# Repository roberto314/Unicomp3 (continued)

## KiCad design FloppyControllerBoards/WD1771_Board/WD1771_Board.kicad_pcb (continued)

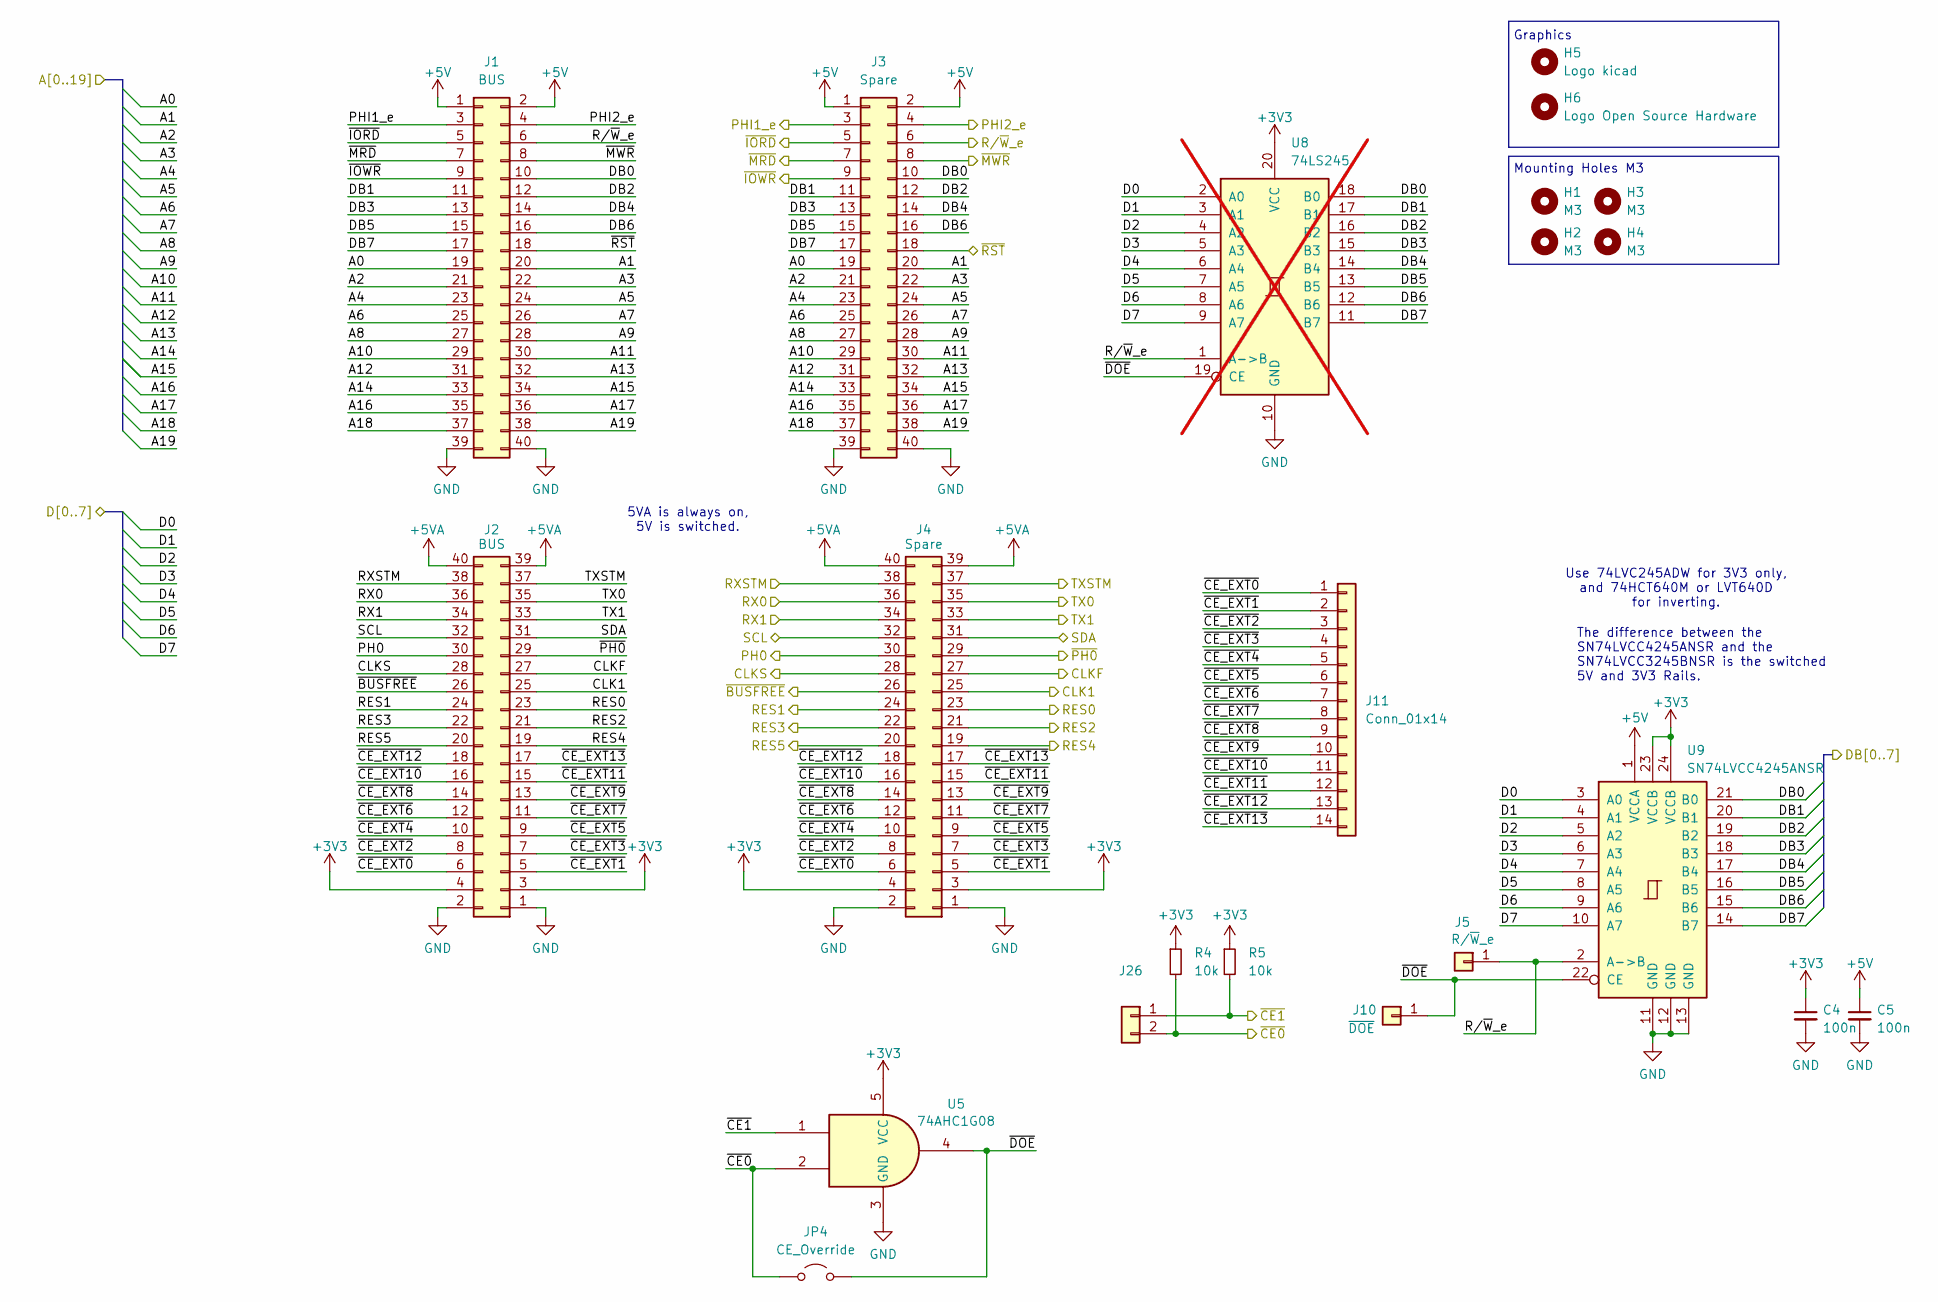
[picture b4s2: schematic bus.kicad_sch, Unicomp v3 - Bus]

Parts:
C4, C5: 100n; C_1206_3216Metric
H1, H2, H3, H4: M3; MountingHole_3.2mm_M3
H5: Logo kicad; KiCad-Logo2_6mm_SilkScreen
H6: Logo Open Source Hardware; OSHW-Logo2_7.3x6mm_SilkScreen
J1, J2: BUS; PinSocket_2x20_P2.54mm_Vertical
J3, J4: Spare; PinSocket_2x20_P2.54mm_Vertical
J5: R/~{W}_e; PinHeader_1x01_P2.00mm_Vertical
J10: ~{DOE}; PinHeader_1x01_P2.00mm_Vertical
J11: Conn_01x14; PinSocket_1x14_P2.54mm_Vertical
J26: Conn_01x02; PinSocket_1x02_P2.54mm_Vertical
JP4: CE_Override; SolderJumper-2_P1.3mm_Open_RoundedPad1.0x1.5mm
R4, R5: 10k; R_1206_3216Metric_Pad1.30x1.75mm_HandSolder
U5: 74AHC1G08; SOT-23-5_HandSoldering
U8: 74LS245; SOIC-20W_7.5x12.8mm_P1.27mm; not fitted
U9: SN74LVCC4245ANSR; SO-24_5.3x15mm_P1.27mm

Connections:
+3V3: C4.1, J2.3, J2.4, J4.3, J4.4, R4.1, R5.1, U5.5 (VCC), U8.20 (VCC), U9.23 (VCCB), U9.24 (VCCB); also elsewhere on the board
+5V: C5.1, J1.1, J1.2, J3.1, J3.2, U9.1 (VCCA); also elsewhere on the board
+5VA: J2.39, J2.40, J4.39, J4.40; also elsewhere on the board
/A0: J1.19, J3.19; also elsewhere on the board
/A1: J1.20, J3.20; also elsewhere on the board
/A2: J1.21, J3.21
/A3: J1.22, J3.22; also elsewhere on the board
/A4: J1.23, J3.23
/A5: J1.24, J3.24
/A6: J1.25, J3.25
/A7: J1.26, J3.26
/A8: J1.27, J3.27
/A9: J1.28, J3.28
/A10: J1.29, J3.29
/A11: J1.30, J3.30
/A12: J1.31, J3.31
/A13: J1.32, J3.32
/A14: J1.33, J3.33
/A15: J1.34, J3.34
/A16: J1.35, J3.35
/A17: J1.36, J3.36
/A18: J1.37, J3.37
/A19: J1.38, J3.38
/Bus/~CE_EXT0: J2.6, J4.6, J11.1
/Bus/~CE_EXT1: J2.5, J4.5, J11.2
/Bus/~CE_EXT2: J2.8, J4.8, J11.3
/Bus/~CE_EXT3: J2.7, J4.7, J11.4
/Bus/~CE_EXT4: J2.10, J4.10, J11.5
/Bus/~CE_EXT5: J2.9, J4.9, J11.6
/Bus/~CE_EXT6: J2.12, J4.12, J11.7
/Bus/~CE_EXT7: J2.11, J4.11, J11.8
/Bus/~CE_EXT8: J2.14, J4.14, J11.9
/Bus/~CE_EXT9: J2.13, J4.13, J11.10
/Bus/~CE_EXT10: J2.16, J4.16, J11.11
/Bus/~CE_EXT11: J2.15, J4.15, J11.12
/Bus/~CE_EXT12: J2.18, J4.18, J11.13
/Bus/~CE_EXT13: J2.17, J4.17, J11.14
/Bus/~DOE: J10.1, JP4.2 (B), U5.4, U8.19 (CE), U9.22 (CE)
/CLK1: J2.25, J4.25; also elsewhere on the board
/CLKF: J2.27, J4.27
/CLKS: J2.28, J4.28
/D0: U8.2 (A0), U9.3 (A0); also elsewhere on the board
/D1: U8.3 (A1), U9.4 (A1); also elsewhere on the board
/D2: U8.4 (A2), U9.5 (A2); also elsewhere on the board
/D3: U8.5 (A3), U9.6 (A3); also elsewhere on the board
/D4: U8.6 (A4), U9.7 (A4); also elsewhere on the board
/D5: U8.7 (A5), U9.8 (A5); also elsewhere on the board
/D6: U8.8 (A6), U9.9 (A6); also elsewhere on the board
/D7: U8.9 (A7), U9.10 (A7); also elsewhere on the board
/DB0: J1.10, J3.10, U8.18 (B0), U9.21 (B0); also elsewhere on the board
/DB1: J1.11, J3.11, U8.17 (B1), U9.20 (B1); also elsewhere on the board
/DB2: J1.12, J3.12, U8.16 (B2), U9.19 (B2); also elsewhere on the board
/DB3: J1.13, J3.13, U8.15 (B3), U9.18 (B3); also elsewhere on the board
/DB4: J1.14, J3.14, U8.14 (B4), U9.17 (B4); also elsewhere on the board
/DB5: J1.15, J3.15, U8.13 (B5), U9.16 (B5); also elsewhere on the board
/DB6: J1.16, J3.16, U8.12 (B6), U9.15 (B6); also elsewhere on the board
/DB7: J1.17, J3.17, U8.11 (B7), U9.14 (B7); also elsewhere on the board
/PH0: J2.30, J4.30
/PHI1_e: J1.3, J3.3
/PHI2_e: J1.4, J3.4; also elsewhere on the board
/RES0: J2.23, J4.23
/RES1: J2.24, J4.24
/RES2: J2.21, J4.21
/RES3: J2.22, J4.22
/RES4: J2.19, J4.19
/RES5: J2.20, J4.20
/RX0: J2.36, J4.36
/RX1: J2.34, J4.34
/RXSTM: J2.38, J4.38
/R/~W_e: J1.6, J3.6, J5.1, U8.1 (A->B), U9.2 (A->B); also elsewhere on the board
/SCL: J2.32, J4.32
/SDA: J2.31, J4.31
/TX0: J2.35, J4.35
/TX1: J2.33, J4.33
/TXSTM: J2.37, J4.37
/ZZ27: J26.2, JP4.1 (A), R4.2, U5.2; also elsewhere on the board
/ZZ40: J1.18, J3.18; also elsewhere on the board
/~BUSFREE: J2.26, J4.26
/~CE1: J26.1, R5.2, U5.1
/~IORD: J1.5, J3.5; also elsewhere on the board
/~IOWR: J1.9, J3.9; also elsewhere on the board
/~MRD: J1.7, J3.7
/~MWR: J1.8, J3.8
/~PH0: J2.29, J4.29
GND: C4.2, C5.2, J1.39, J1.40, J2.1, J2.2, J3.39, J3.40, J4.1, J4.2, U5.3 (GND), U8.10 (GND), U9.11 (GND), U9.12 (GND), U9.13 (GND); also elsewhere on the board

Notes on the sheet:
Graphics
5VA is always on, 5V is switched.
Use 74LVC245ADW for 3V3 only, and 74HCT640M or LVT640D for inverting.
Mounting Holes M3
The difference between the SN74LVCC4245ANSR and the SN74LVCC3245BNSR is the switched 5V and 3V3 Rails.

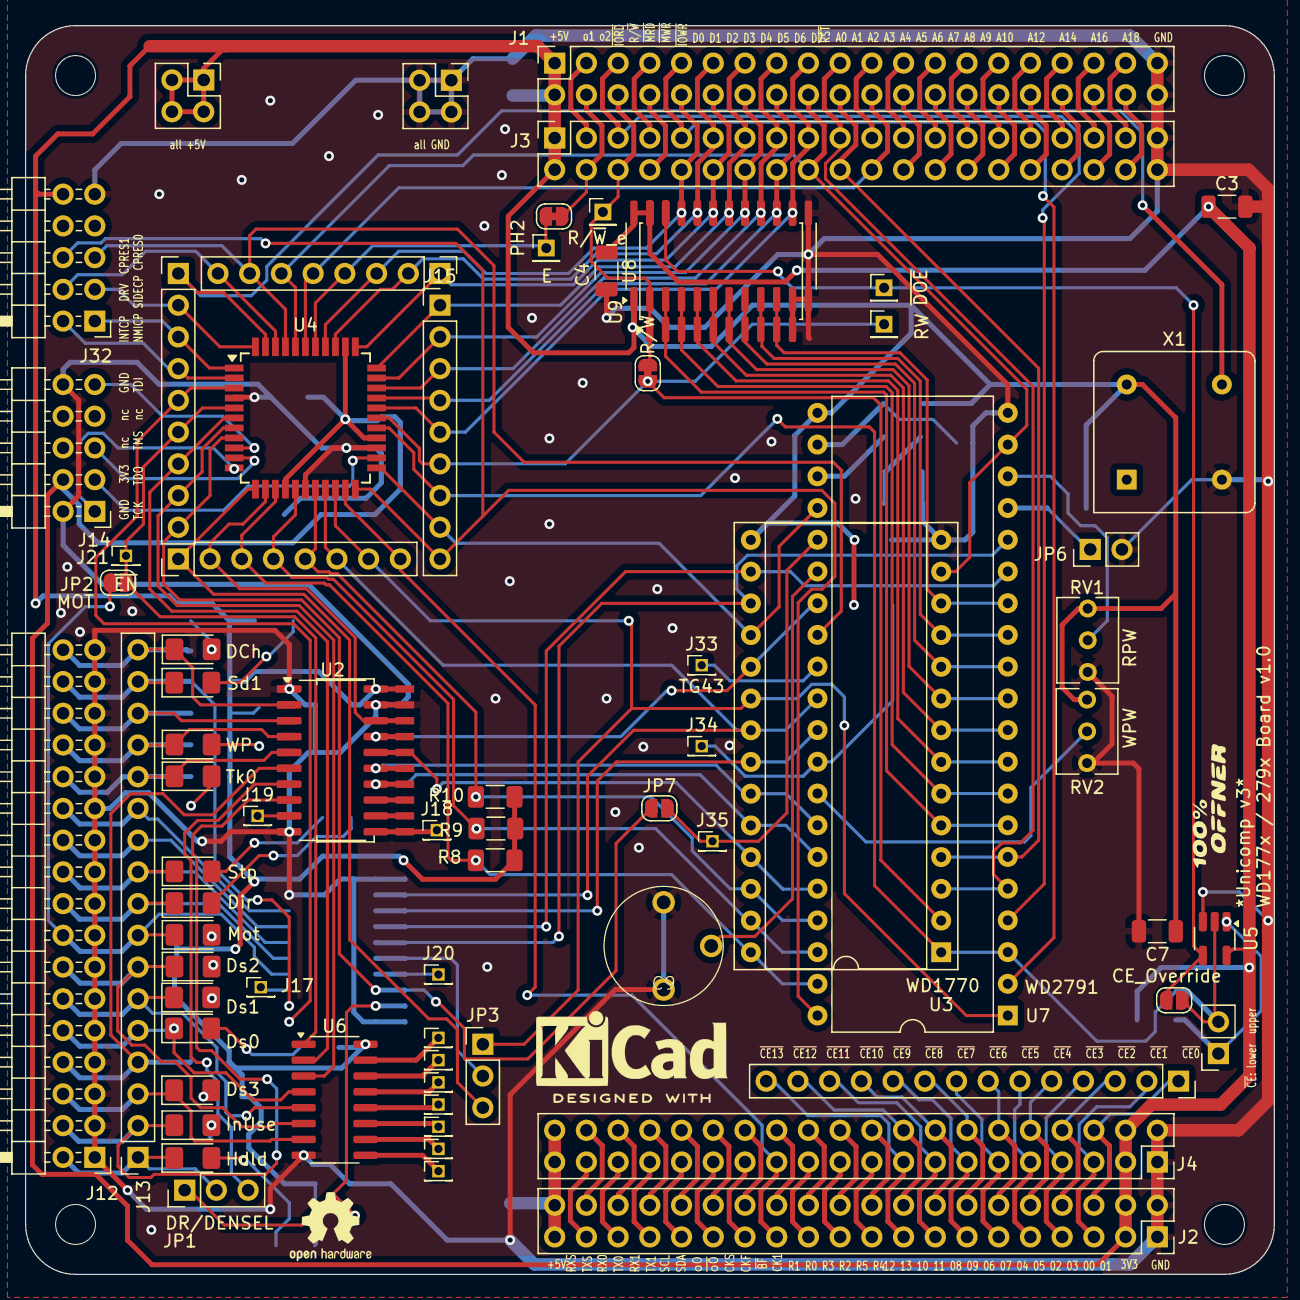
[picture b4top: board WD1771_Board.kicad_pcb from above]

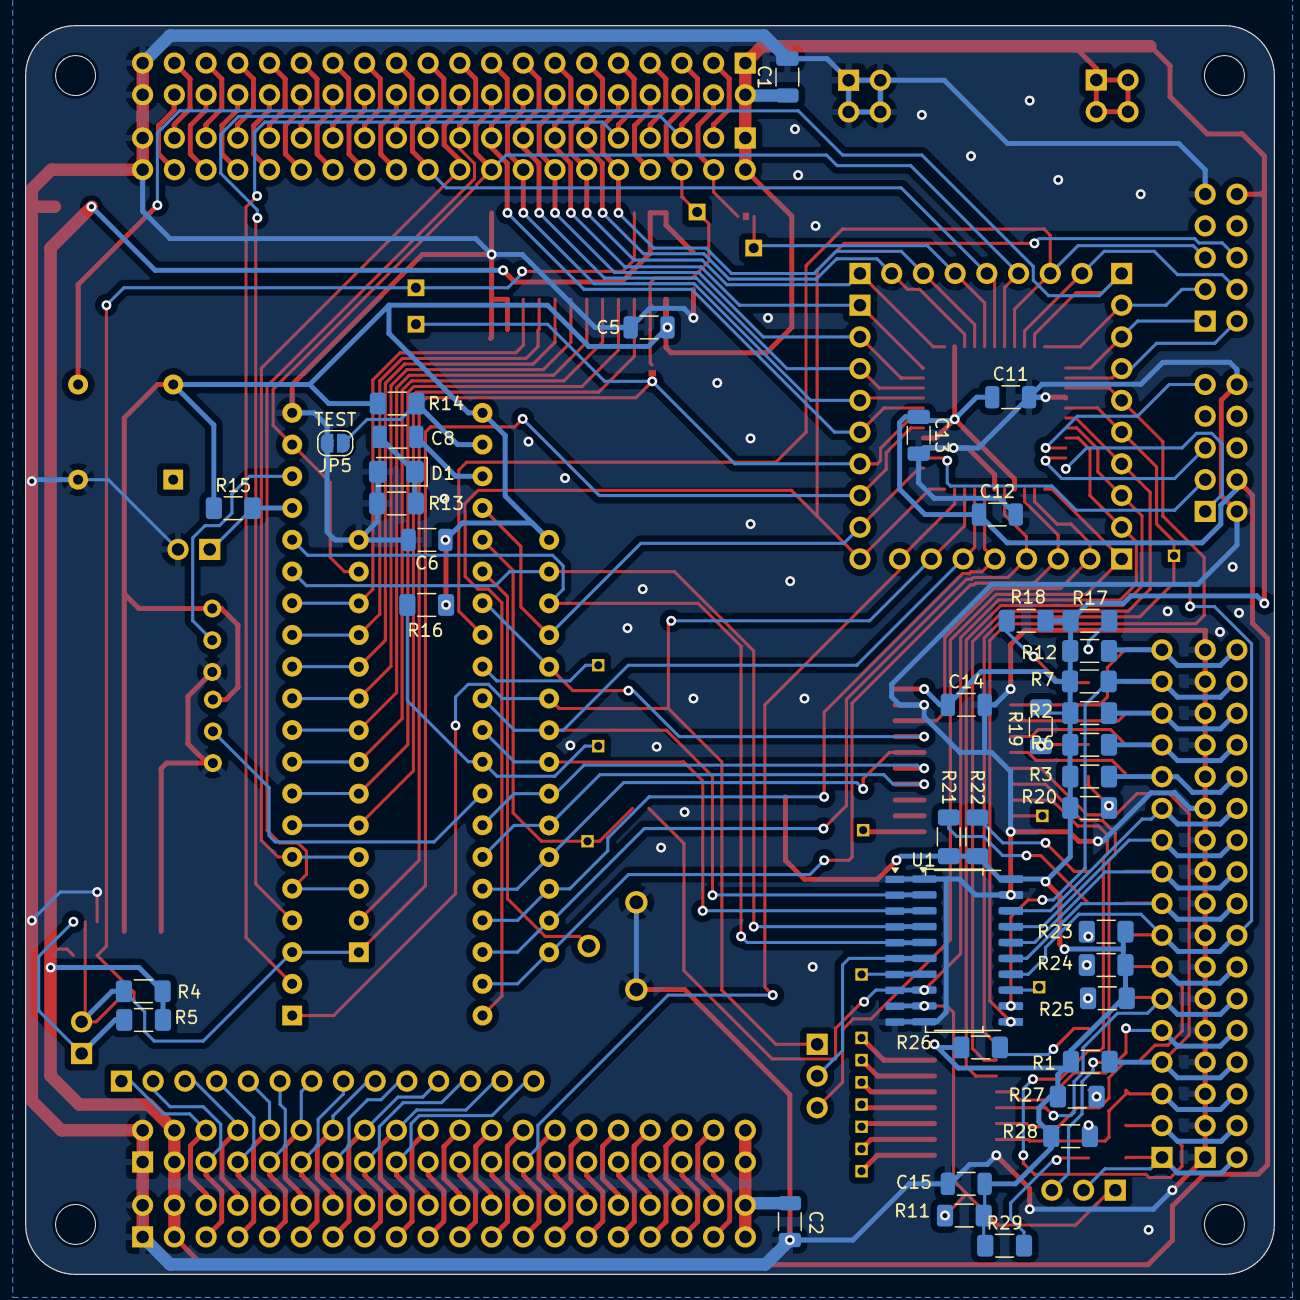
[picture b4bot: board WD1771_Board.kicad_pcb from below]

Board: 2 copper layers, 100.0 x 100.0 mm, 121 parts (40 on the bottom side), 174 nets.

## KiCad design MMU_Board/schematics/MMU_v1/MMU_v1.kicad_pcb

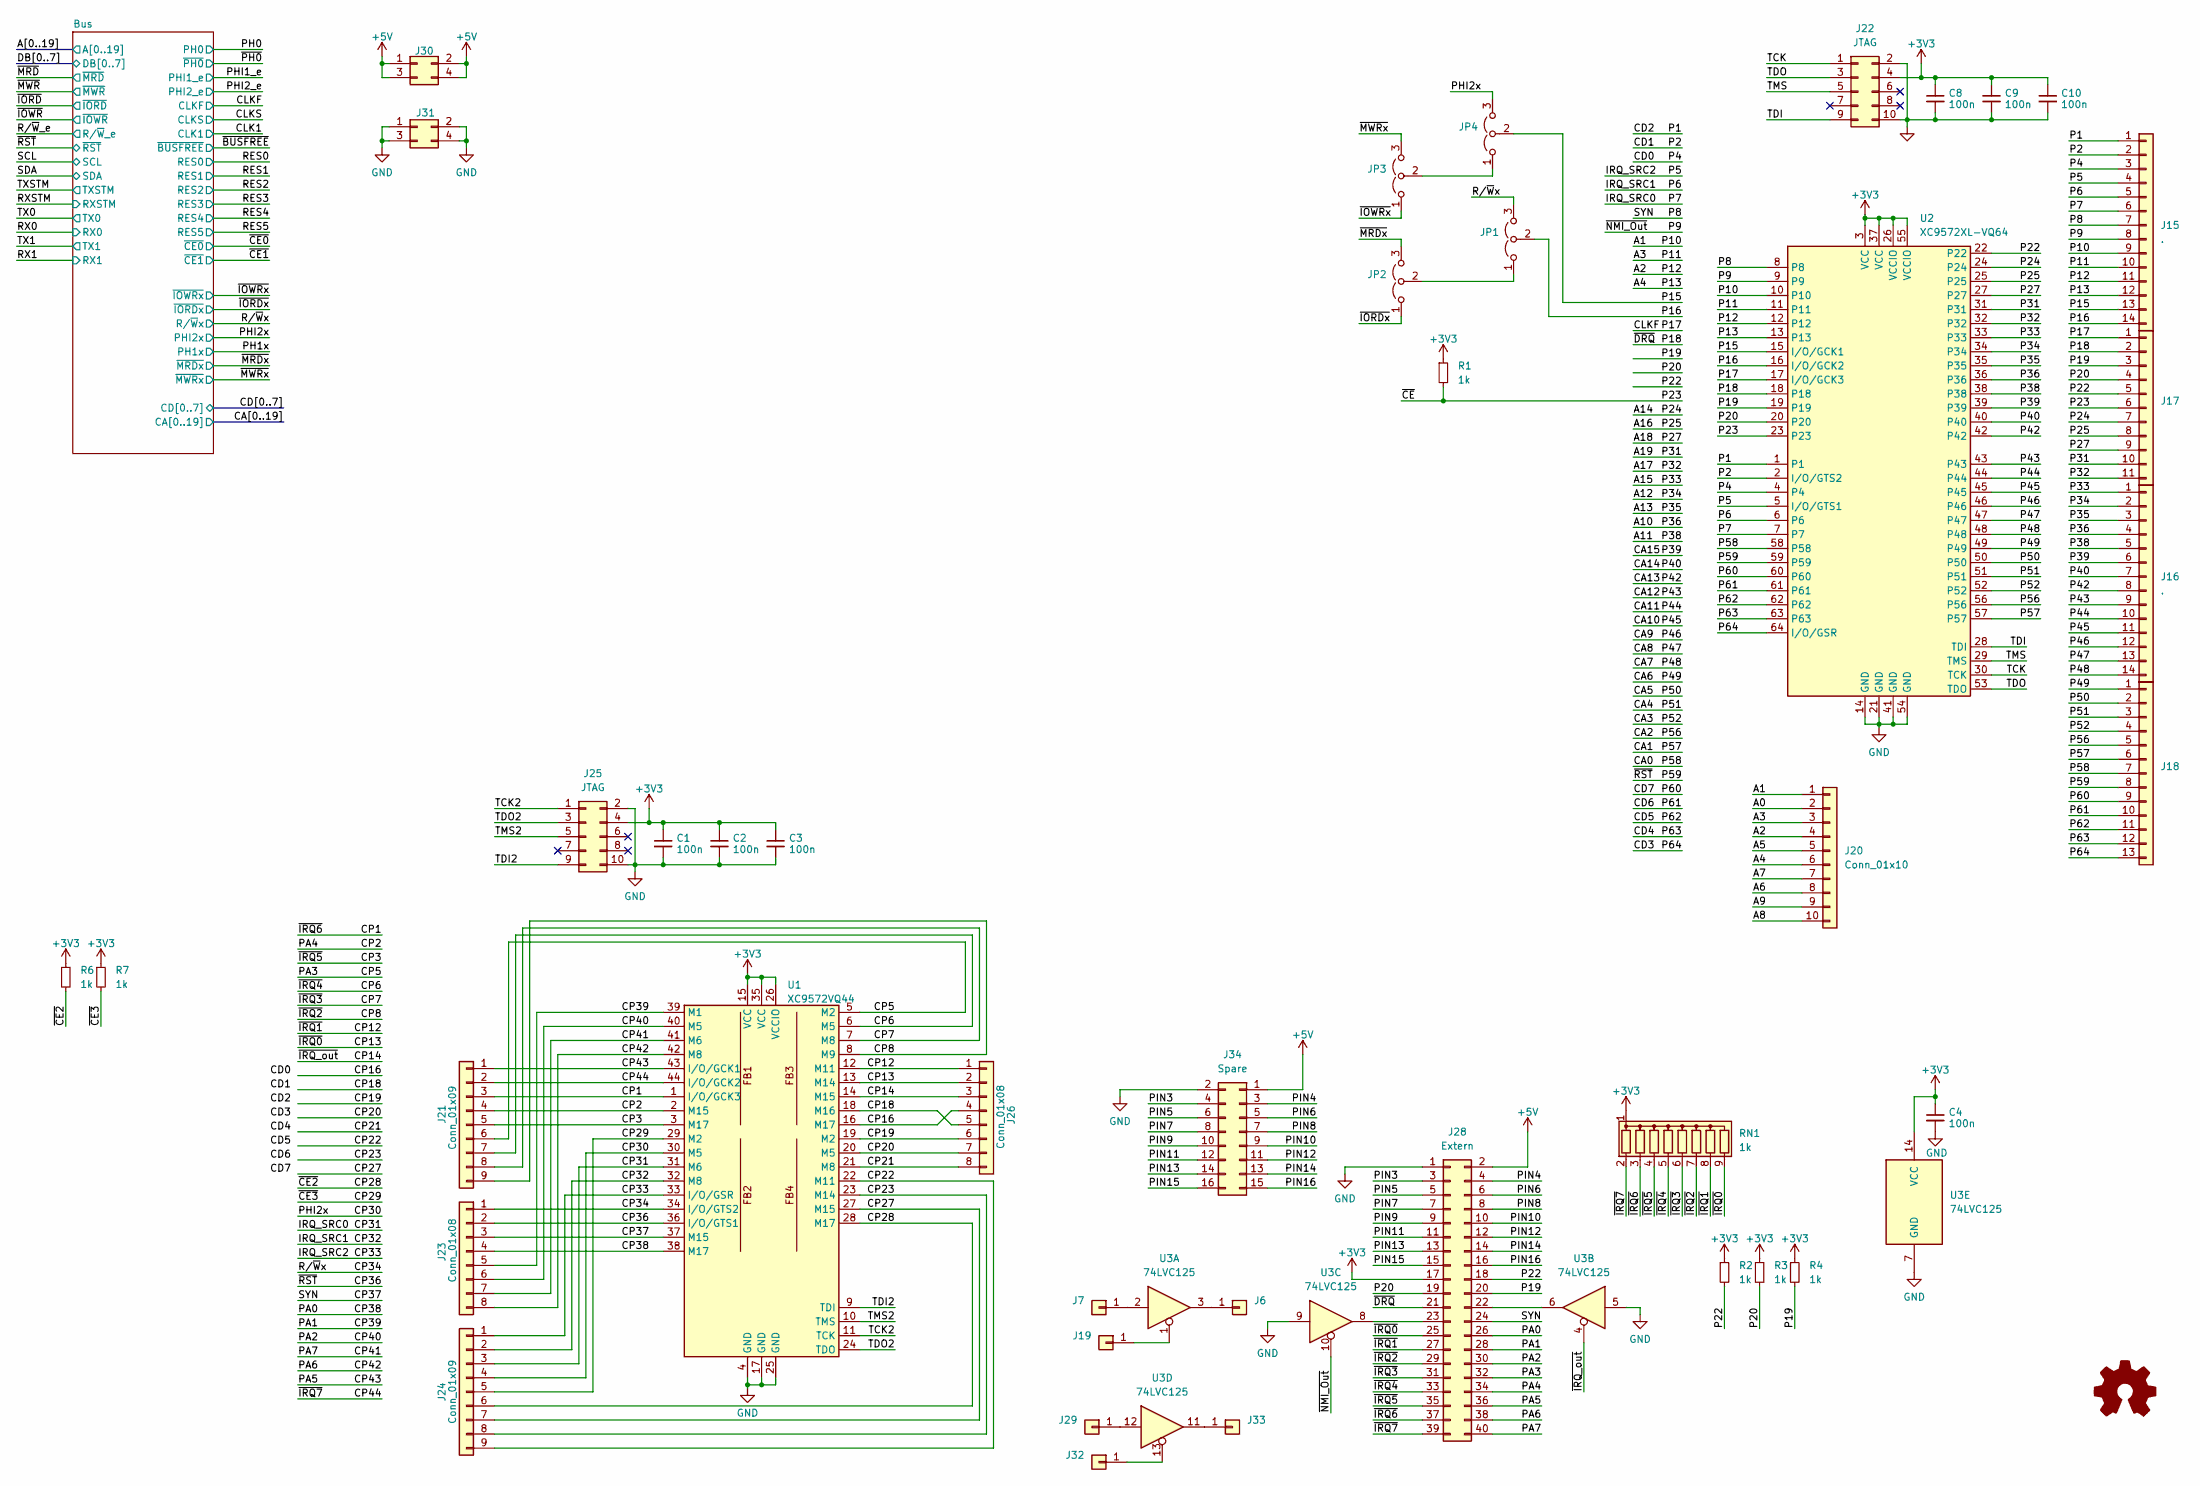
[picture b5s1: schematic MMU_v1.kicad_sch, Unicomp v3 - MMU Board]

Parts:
C1, C2, C3, C4, C8, C9, C10: 100n; C_1206_3216Metric
J6, J7, J19, J29, J32, J33: Conn_01x01; PinSocket_1x01_P1.27mm_Vertical
J15, J16: .; PinSocket_1x14_P2.00mm_Vertical
J17: Conn_01x11; PinSocket_1x11_P2.00mm_Vertical
J18: Conn_01x13; PinSocket_1x13_P2.00mm_Vertical
J20: Conn_01x10; PinSocket_1x10_P2.00mm_Vertical
J21, J24: Conn_01x09; PinHeader_1x09_P2.54mm_Vertical
J22, J25: JTAG; PinHeader_2x05_P2.54mm_Horizontal
J23, J26: Conn_01x08; PinHeader_1x08_P2.54mm_Vertical
J28: Extern; PinHeader_2x20_P2.54mm_Horizontal
J30, J31: Conn_02x02_Odd_Even; PinSocket_2x02_P2.54mm_Vertical
J34: Spare; PinSocket_2x08_P2.54mm_Vertical
JP1, JP2, JP3, JP4: Jumper_3_Open; SolderJumper-3_P1.3mm_Open_RoundedPad1.0x1.5mm
R1, R2, R3, R4, R6, R7: 1k; R_1206_3216Metric_Pad1.30x1.75mm_HandSolder
RN1: 1k; R_Array_SIP9
U1: XC9572VQ44; TQFP-44_10x10mm_P0.8mm
U2: XC9572XL-VQ64; TQFP-64_10x10mm_P0.5mm
U3: 74LVC125; SOIC-14_3.9x8.7mm_P1.27mm

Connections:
+3V3: C1.1, C2.1, C3.1, C4.1, C8.1, C9.1, C10.1, J22.4, J25.4, J28.17, R1.1, R2.1, R3.1, R4.1, R6.1, R7.1, RN1.1 (common), U1.15 (VCC), U1.26 (VCCIO), U1.35 (VCC), U2.3 (VCC), U2.26 (VCCIO), U2.37 (VCC), U2.55 (VCCIO), U3.14 (VCC); also elsewhere on the board
+5V: J28.2, J30.1, J30.2, J30.3, J30.4, J34.1; also elsewhere on the board
/A0: J20.2; also elsewhere on the board
/A1: J15.9, J20.1, U2.10; also elsewhere on the board
/A2: J15.11, J20.4, U2.12; also elsewhere on the board
/A3: J15.10, J20.3, U2.11; also elsewhere on the board
/A4: J15.12, J20.6, U2.13; also elsewhere on the board
/A5: J20.5; also elsewhere on the board
/A6: J20.8; also elsewhere on the board
/A7: J20.7; also elsewhere on the board
/A8: J20.10; also elsewhere on the board
/A9: J20.9; also elsewhere on the board
/A10: J16.4, U2.36; also elsewhere on the board
/A11: J16.5, U2.38; also elsewhere on the board
/A12: J16.2, U2.34; also elsewhere on the board
/A13: J16.3, U2.35; also elsewhere on the board
/A14: J17.7, U2.24; also elsewhere on the board
/A15: J16.1, U2.33; also elsewhere on the board
/A16: J17.8, U2.25; also elsewhere on the board
/A17: J17.11, U2.32; also elsewhere on the board
/A18: J17.9, U2.27; also elsewhere on the board
/A19: J17.10, U2.31; also elsewhere on the board
/CA0: J18.7, U2.58; also elsewhere on the board
/CA1: J18.6, U2.57; also elsewhere on the board
/CA2: J18.5, U2.56; also elsewhere on the board
/CA3: J18.4, U2.52; also elsewhere on the board
/CA4: J18.3, U2.51; also elsewhere on the board
/CA5: J18.2, U2.50; also elsewhere on the board
/CA6: J18.1, U2.49; also elsewhere on the board
/CA7: J16.14, U2.48; also elsewhere on the board
/CA8: J16.13, U2.47; also elsewhere on the board
/CA9: J16.12, U2.46; also elsewhere on the board
/CA10: J16.11, U2.45; also elsewhere on the board
/CA11: J16.10, U2.44; also elsewhere on the board
/CA12: J16.9, U2.43; also elsewhere on the board
/CA13: J16.8, U2.42; also elsewhere on the board
/CA14: J16.7, U2.40; also elsewhere on the board
/CA15: J16.6, U2.39; also elsewhere on the board
/CD0: J15.3, U2.4; also elsewhere on the board
/CD1: J15.2, U2.2 (I/O/GTS2); also elsewhere on the board
/CD2: J15.1, U2.1; also elsewhere on the board
/CD3: J18.13, U2.64 (I/O/GSR); also elsewhere on the board
/CD4: J18.12, U2.63; also elsewhere on the board
/CD5: J18.11, U2.62; also elsewhere on the board
/CD6: J18.10, U2.61; also elsewhere on the board
/CD7: J18.9, U2.60; also elsewhere on the board
/CLKF: J17.1, U2.17 (I/O/GCK3); also elsewhere on the board
/CP1: J21.3, J28.37, RN1.3 (R2), U1.1 (I/O/GCK3)
/CP2: J21.4, J28.34, U1.2 (M15)
/CP3: J21.5, J28.35, RN1.4 (R3), U1.3 (M17)
/CP5: J21.6, J28.32, U1.5 (M2)
/CP6: J21.7, J28.33, RN1.5 (R4), U1.6 (M5)
/CP7: J21.8, J28.31, RN1.6 (R5), U1.7 (M8)
/CP8: J21.9, J28.29, RN1.7 (R6), U1.8 (M9)
/CP12: J26.1, J28.27, RN1.8 (R7), U1.12 (M11)
/CP13: J26.2, J28.25, RN1.9 (R8), U1.13 (M14)
/CP14: J26.3, U1.14 (M15), U3.4
/CP16: J26.4, U1.16 (M17)
/CP18: J26.5, U1.18 (M16)
/CP19: J26.6, U1.19 (M2)
/CP20: J26.7, U1.20 (M5)
/CP21: J26.8, U1.21 (M8)
/CP22: J24.9, U1.22 (M11)
/CP23: J24.8, U1.23 (M14)
/CP27: J24.7, U1.27 (M15)
/CP28: J24.6, R6.2, U1.28 (M17)
/CP29: J24.5, R7.2, U1.29 (M2)
/CP30: J24.4, JP4.3 (B), U1.30 (M5); also elsewhere on the board
/CP31: J15.6, J24.3, U1.31 (M6), U2.7
/CP32: J15.5, J24.2, U1.32 (M8), U2.6
/CP33: J15.4, J24.1, U1.33 (I/O/GSR), U2.5 (I/O/GTS1)
/CP34: J23.1, JP1.3 (B), U1.34 (I/O/GTS2); also elsewhere on the board
/CP36: J18.8, J23.2, U1.36 (I/O/GTS1), U2.59; also elsewhere on the board
/CP37: J15.7, J23.3, J28.24, U1.37 (M15), U2.8
/CP38: J23.4, J28.26, U1.38 (M17)
/CP39: J23.5, J28.28, U1.39 (M1)
/CP40: J23.6, J28.30, U1.40 (M5)
/CP41: J23.7, J28.40, U1.41 (M6)
/CP42: J23.8, J28.38, U1.42 (M8)
/CP43: J21.1, J28.36, U1.43 (I/O/GCK1)
/CP44: J21.2, J28.39, RN1.2 (R1), U1.44 (I/O/GCK2)
/P9: J15.8, U2.9, U3.10
/P15: J15.13, JP4.2 (C), U2.15 (I/O/GCK1)
/P16: J15.14, JP1.2 (C), U2.16 (I/O/GCK2)
/P18: J17.2, J28.21, U2.18
/P19: J17.3, J28.20, R4.2, U2.19
/P20: J17.4, J28.19, R3.2, U2.20
/P22: J17.5, J28.18, R2.2, U2.22
/P23: J17.6, R1.2, U2.23
/PIN3: J28.3, J34.4
/PIN4: J28.4, J34.3
/PIN5: J28.5, J34.6
/PIN6: J28.6, J34.5
/PIN7: J28.7, J34.8
/PIN8: J28.8, J34.7
/PIN9: J28.9, J34.10
/PIN10: J28.10, J34.9
/PIN11: J28.11, J34.12
/PIN12: J28.12, J34.11
/PIN13: J28.13, J34.14
/PIN14: J28.14, J34.13
/PIN15: J28.15, J34.16
/PIN16: J28.16, J34.15
/TCK: J22.1, U2.30 (TCK)
/TCK2: J25.1, U1.11 (TCK)
/TDI: J22.9, U2.28 (TDI)
/TDI2: J25.9, U1.9 (TDI)
/TDO: J22.3, U2.53 (TDO)
/TDO2: J25.3, U1.24 (TDO)
/TMS: J22.5, U2.29 (TMS)
/TMS2: J25.5, U1.10 (TMS)
/~IORDx: JP2.1 (A); also elsewhere on the board
/~IOWRx: JP3.1 (A); also elsewhere on the board
/~MRDx: JP2.3 (B); also elsewhere on the board
/~MWRx: JP3.3 (B); also elsewhere on the board
GND: C1.2, C2.2, C3.2, C4.2, C8.2, C9.2, C10.2, J22.2, J22.10, J25.2, J25.10, J28.1, J31.1, J31.2, J31.3, J31.4, J34.2, U1.4 (GND), U1.17 (GND), U1.25 (GND), U2.14 (GND), U2.21 (GND), U2.41 (GND), U2.54 (GND), U3.5, U3.7 (GND), U3.9; also elsewhere on the board
unnamed: J6.1, U3.3
unnamed: J7.1, U3.2
unnamed: J19.1, U3.1
unnamed: J28.22, U3.6
unnamed: J28.23, U3.8
unnamed: J29.1, U3.12
unnamed: J32.1, U3.13
unnamed: J33.1, U3.11
unnamed: JP1.1 (A), JP2.2 (C)
unnamed: JP3.2 (C), JP4.1 (A)

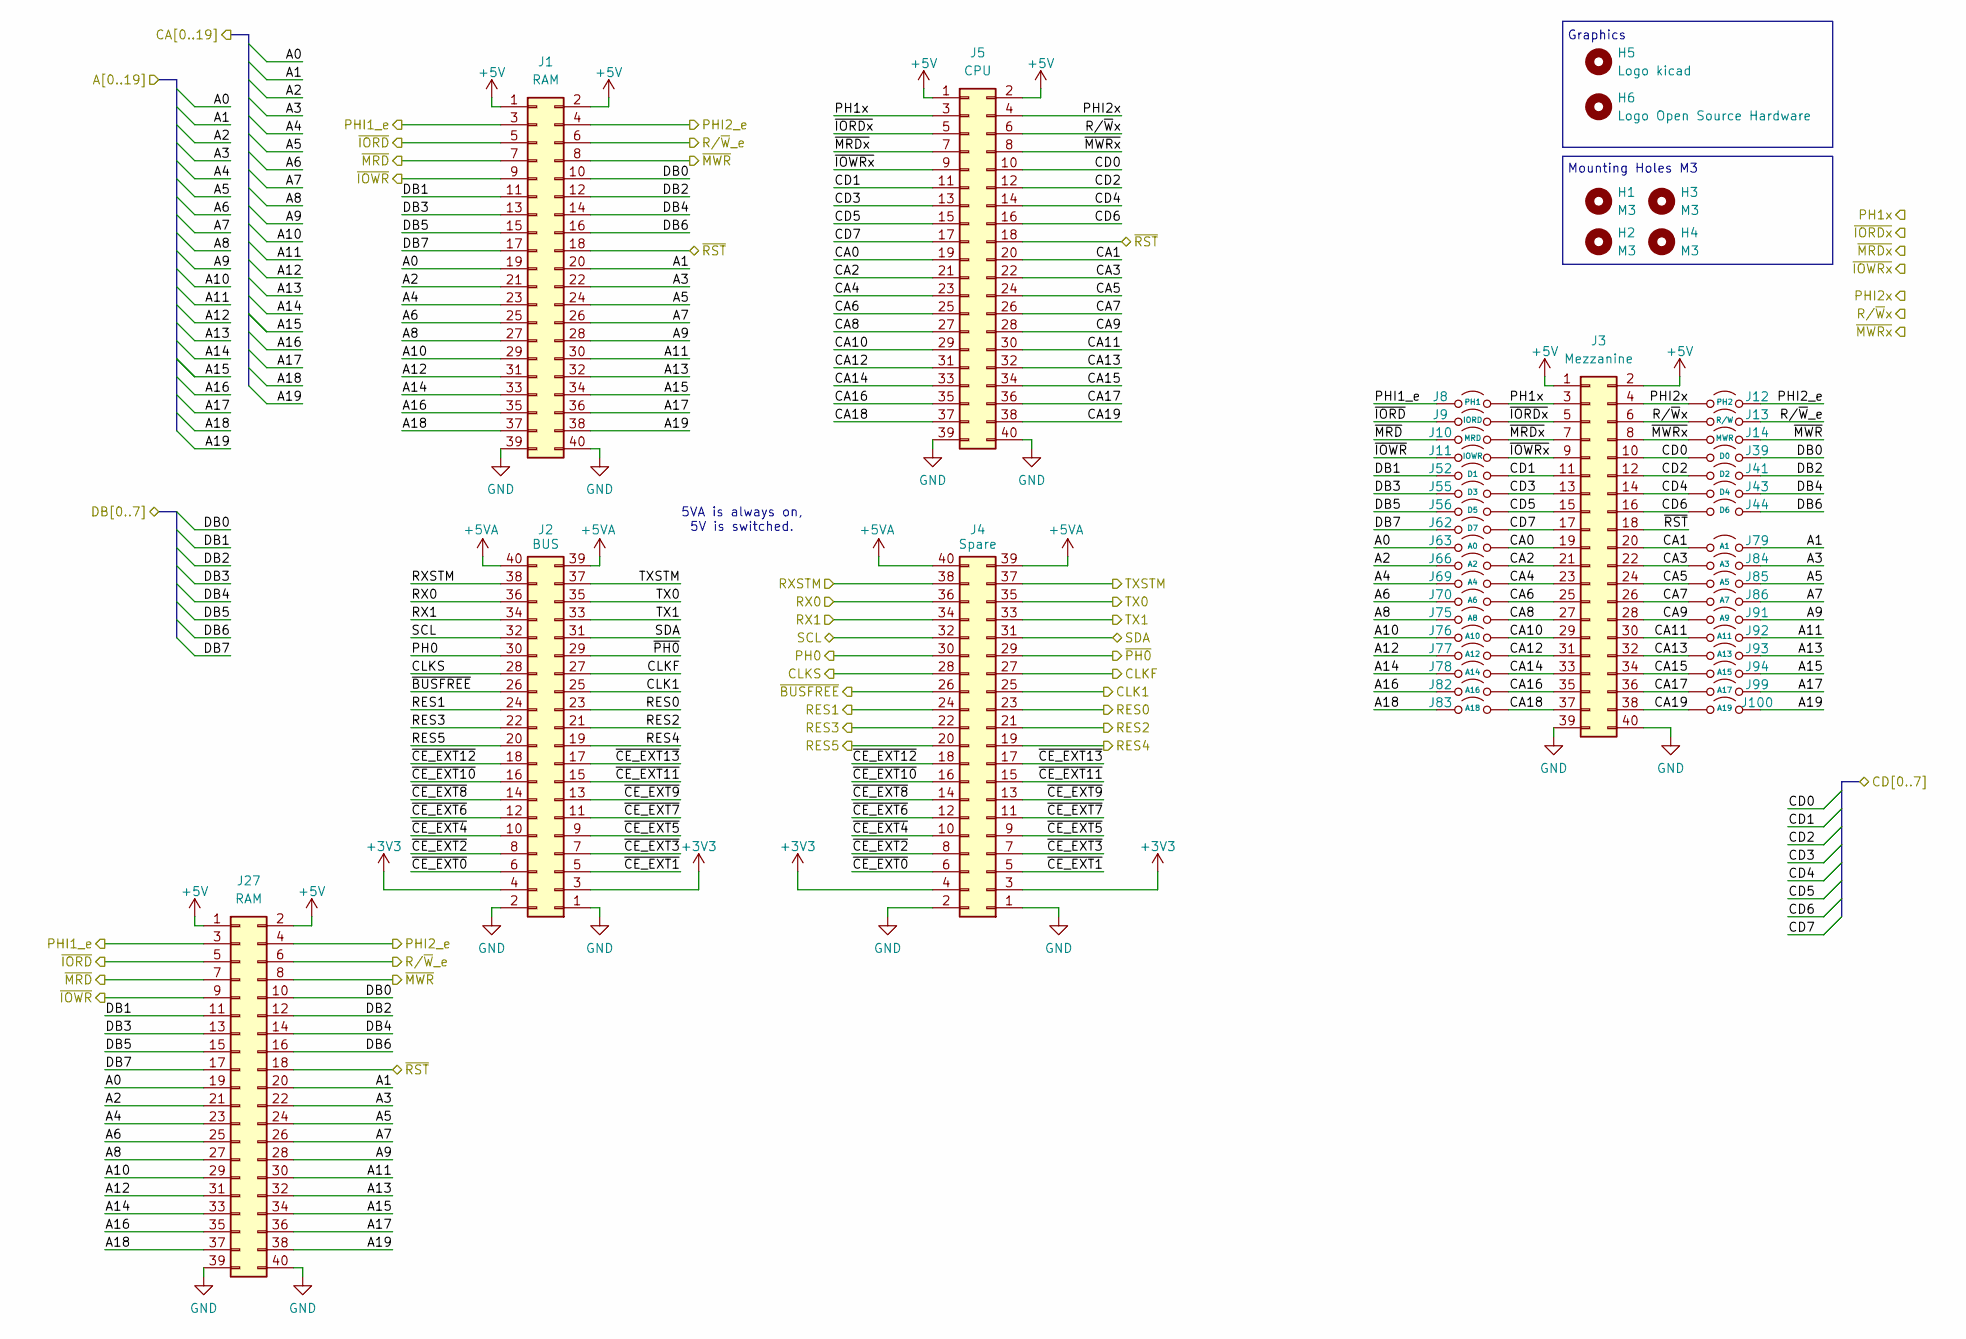
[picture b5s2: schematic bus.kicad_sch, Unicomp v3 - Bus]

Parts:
H1, H2, H3, H4: M3; MountingHole_3.2mm_M3
H5: Logo kicad; KiCad-Logo2_6mm_SilkScreen
H6: Logo Open Source Hardware; OSHW-Logo2_7.3x6mm_SilkScreen
J1, J27: RAM; PinSocket_2x20_P2.54mm_Vertical
J2: BUS; PinSocket_2x20_P2.54mm_Vertical
J3: Mezzanine; PinSocket_2x20_P2.54mm_Vertical_SMD
J4: Spare; PinSocket_2x20_P2.54mm_Vertical
J5: CPU; PinSocket_2x20_P2.54mm_Vertical
J8: PH1; SolderJumper-2_P1.3mm_Open_RoundedPad1.0x1.5mm
J9: IORD; SolderJumper-2_P1.3mm_Open_RoundedPad1.0x1.5mm
J10: MRD; SolderJumper-2_P1.3mm_Open_RoundedPad1.0x1.5mm
J11: IOWR; SolderJumper-2_P1.3mm_Open_RoundedPad1.0x1.5mm
J12: PH2; SolderJumper-2_P1.3mm_Open_RoundedPad1.0x1.5mm
J13: R/W; SolderJumper-2_P1.3mm_Open_RoundedPad1.0x1.5mm
J14: MWR; SolderJumper-2_P1.3mm_Open_RoundedPad1.0x1.5mm
J39: D0; SolderJumper-2_P1.3mm_Open_RoundedPad1.0x1.5mm
J41: D2; SolderJumper-2_P1.3mm_Open_RoundedPad1.0x1.5mm
J43: D4; SolderJumper-2_P1.3mm_Open_RoundedPad1.0x1.5mm
J44: D6; SolderJumper-2_P1.3mm_Open_RoundedPad1.0x1.5mm
J52: D1; SolderJumper-2_P1.3mm_Open_RoundedPad1.0x1.5mm
J55: D3; SolderJumper-2_P1.3mm_Open_RoundedPad1.0x1.5mm
J56: D5; SolderJumper-2_P1.3mm_Open_RoundedPad1.0x1.5mm
J62: D7; SolderJumper-2_P1.3mm_Open_RoundedPad1.0x1.5mm
J63: A0; SolderJumper-2_P1.3mm_Open_RoundedPad1.0x1.5mm
J66: A2; SolderJumper-2_P1.3mm_Open_RoundedPad1.0x1.5mm
J69: A4; SolderJumper-2_P1.3mm_Open_RoundedPad1.0x1.5mm
J70: A6; SolderJumper-2_P1.3mm_Open_RoundedPad1.0x1.5mm
J75: A8; SolderJumper-2_P1.3mm_Open_RoundedPad1.0x1.5mm
J76: A10; SolderJumper-2_P1.3mm_Open_RoundedPad1.0x1.5mm
J77: A12; SolderJumper-2_P1.3mm_Open_RoundedPad1.0x1.5mm
J78: A14; SolderJumper-2_P1.3mm_Open_RoundedPad1.0x1.5mm
J79: A1; SolderJumper-2_P1.3mm_Open_RoundedPad1.0x1.5mm
J82: A16; SolderJumper-2_P1.3mm_Open_RoundedPad1.0x1.5mm
J83: A18; SolderJumper-2_P1.3mm_Open_RoundedPad1.0x1.5mm
J84: A3; SolderJumper-2_P1.3mm_Open_RoundedPad1.0x1.5mm
J85: A5; SolderJumper-2_P1.3mm_Open_RoundedPad1.0x1.5mm
J86: A7; SolderJumper-2_P1.3mm_Open_RoundedPad1.0x1.5mm
J91: A9; SolderJumper-2_P1.3mm_Open_RoundedPad1.0x1.5mm
J92: A11; SolderJumper-2_P1.3mm_Open_RoundedPad1.0x1.5mm
J93: A13; SolderJumper-2_P1.3mm_Open_RoundedPad1.0x1.5mm
J94: A15; SolderJumper-2_P1.3mm_Open_RoundedPad1.0x1.5mm
J99: A17; SolderJumper-2_P1.3mm_Open_RoundedPad1.0x1.5mm
J100: A19; SolderJumper-2_P1.3mm_Open_RoundedPad1.0x1.5mm

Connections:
+3V3: J2.3, J2.4, J4.3, J4.4; also elsewhere on the board
+5V: J1.1, J1.2, J3.1, J3.2, J5.1, J5.2, J27.1, J27.2; also elsewhere on the board
+5VA: J2.39, J2.40, J4.39, J4.40
/A0: J1.19, J27.19, J63.1 (A); also elsewhere on the board
/A1: J1.20, J27.20, J79.1 (A); also elsewhere on the board
/A2: J1.21, J27.21, J66.1 (A); also elsewhere on the board
/A3: J1.22, J27.22, J84.1 (A); also elsewhere on the board
/A4: J1.23, J27.23, J69.1 (A); also elsewhere on the board
/A5: J1.24, J27.24, J85.1 (A); also elsewhere on the board
/A6: J1.25, J27.25, J70.1 (A); also elsewhere on the board
/A7: J1.26, J27.26, J86.1 (A); also elsewhere on the board
/A8: J1.27, J27.27, J75.1 (A); also elsewhere on the board
/A9: J1.28, J27.28, J91.1 (A); also elsewhere on the board
/A10: J1.29, J27.29, J76.1 (A); also elsewhere on the board
/A11: J1.30, J27.30, J92.1 (A); also elsewhere on the board
/A12: J1.31, J27.31, J77.1 (A); also elsewhere on the board
/A13: J1.32, J27.32, J93.1 (A); also elsewhere on the board
/A14: J1.33, J27.33, J78.1 (A); also elsewhere on the board
/A15: J1.34, J27.34, J94.1 (A); also elsewhere on the board
/A16: J1.35, J27.35, J82.1 (A); also elsewhere on the board
/A17: J1.36, J27.36, J99.1 (A); also elsewhere on the board
/A18: J1.37, J27.37, J83.1 (A); also elsewhere on the board
/A19: J1.38, J27.38, J100.1 (A); also elsewhere on the board
/Bus/~CE_EXT0: J2.6, J4.6
/Bus/~CE_EXT1: J2.5, J4.5
/Bus/~CE_EXT2: J2.8, J4.8
/Bus/~CE_EXT3: J2.7, J4.7
/Bus/~CE_EXT4: J2.10, J4.10
/Bus/~CE_EXT5: J2.9, J4.9
/Bus/~CE_EXT6: J2.12, J4.12
/Bus/~CE_EXT7: J2.11, J4.11
/Bus/~CE_EXT8: J2.14, J4.14
/Bus/~CE_EXT9: J2.13, J4.13
/Bus/~CE_EXT10: J2.16, J4.16
/Bus/~CE_EXT11: J2.15, J4.15
/Bus/~CE_EXT12: J2.18, J4.18
/Bus/~CE_EXT13: J2.17, J4.17
/CA0: J3.19, J5.19, J63.2 (B); also elsewhere on the board
/CA1: J3.20, J5.20, J79.2 (B); also elsewhere on the board
/CA2: J3.21, J5.21, J66.2 (B); also elsewhere on the board
/CA3: J3.22, J5.22, J84.2 (B); also elsewhere on the board
/CA4: J3.23, J5.23, J69.2 (B); also elsewhere on the board
/CA5: J3.24, J5.24, J85.2 (B); also elsewhere on the board
/CA6: J3.25, J5.25, J70.2 (B); also elsewhere on the board
/CA7: J3.26, J5.26, J86.2 (B); also elsewhere on the board
/CA8: J3.27, J5.27, J75.2 (B); also elsewhere on the board
/CA9: J3.28, J5.28, J91.2 (B); also elsewhere on the board
/CA10: J3.29, J5.29, J76.2 (B); also elsewhere on the board
/CA11: J3.30, J5.30, J92.2 (B); also elsewhere on the board
/CA12: J3.31, J5.31, J77.2 (B); also elsewhere on the board
/CA13: J3.32, J5.32, J93.2 (B); also elsewhere on the board
/CA14: J3.33, J5.33, J78.2 (B); also elsewhere on the board
/CA15: J3.34, J5.34, J94.2 (B); also elsewhere on the board
/CA16: J3.35, J5.35, J82.2 (B)
/CA17: J3.36, J5.36, J99.2 (B)
/CA18: J3.37, J5.37, J83.2 (B)
/CA19: J3.38, J5.38, J100.2 (B)
/CD0: J3.10, J5.10, J39.2 (B); also elsewhere on the board
/CD1: J3.11, J5.11, J52.2 (B); also elsewhere on the board
/CD2: J3.12, J5.12, J41.2 (B); also elsewhere on the board
/CD3: J3.13, J5.13, J55.2 (B); also elsewhere on the board
/CD4: J3.14, J5.14, J43.2 (B); also elsewhere on the board
/CD5: J3.15, J5.15, J56.2 (B); also elsewhere on the board
/CD6: J3.16, J5.16, J44.2 (B); also elsewhere on the board
/CD7: J3.17, J5.17, J62.2 (B); also elsewhere on the board
/CLK1: J2.25, J4.25
/CLKF: J2.27, J4.27; also elsewhere on the board
/CLKS: J2.28, J4.28
/CP30: J3.4, J5.4, J12.2 (B); also elsewhere on the board
/CP34: J3.6, J5.6, J13.2 (B); also elsewhere on the board
/CP36: J1.18, J3.18, J5.18, J27.18; also elsewhere on the board
/DB0: J1.10, J27.10, J39.1 (A)
/DB1: J1.11, J27.11, J52.1 (A)
/DB2: J1.12, J27.12, J41.1 (A)
/DB3: J1.13, J27.13, J55.1 (A)
/DB4: J1.14, J27.14, J43.1 (A)
/DB5: J1.15, J27.15, J56.1 (A)
/DB6: J1.16, J27.16, J44.1 (A)
/DB7: J1.17, J27.17, J62.1 (A)
/PH0: J2.30, J4.30
/PH1x: J3.3, J5.3, J8.2 (B)
/PHI1_e: J1.3, J8.1 (A), J27.3
/PHI2_e: J1.4, J12.1 (A), J27.4
/RES0: J2.23, J4.23
/RES1: J2.24, J4.24
/RES2: J2.21, J4.21
/RES3: J2.22, J4.22
/RES4: J2.19, J4.19
/RES5: J2.20, J4.20
/RX0: J2.36, J4.36
/RX1: J2.34, J4.34
/RXSTM: J2.38, J4.38
/R/~W_e: J1.6, J13.1 (A), J27.6
/SCL: J2.32, J4.32
/SDA: J2.31, J4.31
/TX0: J2.35, J4.35
/TX1: J2.33, J4.33
/TXSTM: J2.37, J4.37
/~BUSFREE: J2.26, J4.26
/~IORDx: J3.5, J5.5, J9.2 (B); also elsewhere on the board
/~IORD: J1.5, J9.1 (A), J27.5
/~IOWRx: J3.9, J5.9, J11.2 (B); also elsewhere on the board
/~IOWR: J1.9, J11.1 (A), J27.9
/~MRDx: J3.7, J5.7, J10.2 (B); also elsewhere on the board
/~MRD: J1.7, J10.1 (A), J27.7
/~MWRx: J3.8, J5.8, J14.2 (B); also elsewhere on the board
/~MWR: J1.8, J14.1 (A), J27.8
/~PH0: J2.29, J4.29
GND: J1.39, J1.40, J2.1, J2.2, J3.39, J3.40, J4.1, J4.2, J5.39, J5.40, J27.39, J27.40; also elsewhere on the board

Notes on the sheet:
Graphics
5VA is always on, 5V is switched.
Mounting Holes M3
